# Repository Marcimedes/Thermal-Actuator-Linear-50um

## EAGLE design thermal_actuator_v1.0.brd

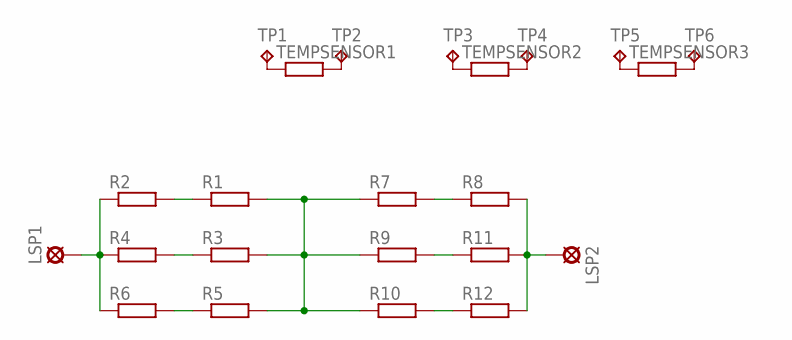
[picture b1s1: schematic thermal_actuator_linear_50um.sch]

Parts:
LSP1, LSP2: LSP10
R1, R2, R3, R4, R5, R6, R7, R8, R9, R10, R11, R12: R-EU_R0402; R0402
TEMPSENSOR1, TEMPSENSOR2, TEMPSENSOR3: R-EU_R0402; R0402
TP1, TP2, TP3, TP4, TP5, TP6: TPTP10R; TP10R

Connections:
unnamed: LSP2.MP, R8.2, R11.2, R12.2
unnamed: LSP1.MP, R2.1, R4.1, R6.1
unnamed: R1.1, R2.2
unnamed: R3.1, R4.2
unnamed: R5.1, R6.2
unnamed: R1.2, R3.2, R5.2, R7.1, R9.1, R10.1
unnamed: TEMPSENSOR1.1, TP1.TP
unnamed: TEMPSENSOR1.2, TP2.TP
unnamed: R9.2, R11.1
unnamed: R7.2, R8.1
unnamed: R10.2, R12.1
unnamed: TEMPSENSOR2.1, TP3.TP
unnamed: TEMPSENSOR2.2, TP4.TP
unnamed: TEMPSENSOR3.1, TP5.TP
unnamed: TEMPSENSOR3.2, TP6.TP

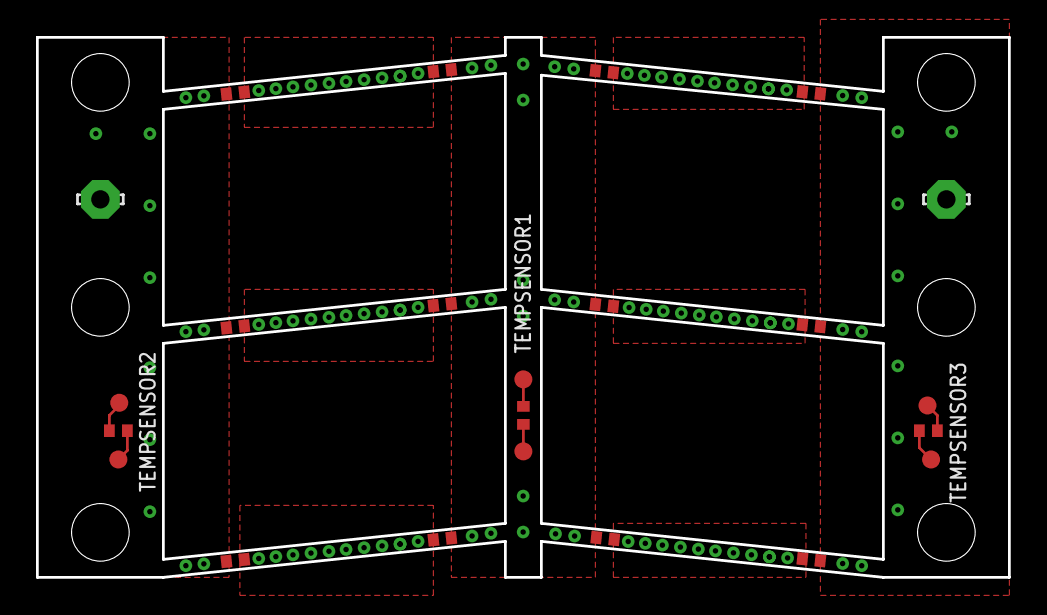
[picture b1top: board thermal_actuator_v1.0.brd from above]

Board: 2 copper layers, 54.0 x 30.0 mm, 23 parts (0 on the bottom side), 15 nets.

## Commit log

2020-11-10 Rename thermal_actuator_v1.0.brd to thermal_actuator_linear_50um.brd
2020-11-10 Rename thermal_actuator_v1.0.sch to thermal_actuator_linear_50um.sch
